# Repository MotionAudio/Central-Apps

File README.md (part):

<div align="center">

# Central

**A pedal for your pads and tracks, and apps for the rest of the worship team.**

[**Download the apps**](https://motionaudio.github.io/Central-Apps/) · [All releases](https://github.com/MotionAudio/Central-Apps/releases/latest) · [Install guide](INSTALL.md) · [What's new](release-notes/HISTORY.md)

</div>

---

I make Central for worship teams. The Central Pedal sits at the worship leader's feet and plays the pads, the multitracks and the click. Central Control runs the lights, slides, lyrics and in-ear mixes from the desk. Every musician gets their own chart and their own mix in Central Usage. This repository has all of it: the pedal's software, the six apps, the website and the tools that build them.

If you just want to install something, go to the [download page](https://motionaudio.github.io/Central-Apps/). It works out which file your computer or phone needs. Every file is also on the [latest release](https://github.com/MotionAudio/Central-Apps/releases/latest).

Sam

## The apps

| | App | Who uses it | What it's for |
|:-:|---|---|---|
|  | **Central Pedal** | The worship leader, on stage | A Raspberry Pi 4 that starts straight into the pedal. It plays ambient pads and multitracks with the click, spoken cues, charts and lyrics, and it can be the guitar or keys rig. You play it with 12 footswitches, knobs, a touch screen, an expression pedal, MIDI or a Stream Deck. |
|  | **Central Pedal Control** | Whoever gets the songs ready | The pedal's app on your computer, tablet or phone. Build the setlist at home, set up the pads and the controls, then press **⇪ Upload** and it all goes to the pedal. |
|  | **Central Control** | The main admin and admins | The desk. Lights, slides, lyrics, cameras, in-ear mixes, the tracks and the mix, for the whole service. |
|  | **Central Usage** | Musicians and singers | Your chord chart, the lyrics, your instrument and your own in-ear mix. |
|  | **Central Services** | Everyone in the church | The schedule. Who's playing which Sunday, and whether they said yes. |
|  | **Central Production** | Anyone who makes sounds | A studio for recording tracks and making loops, pads, instruments, plugins and pedal boards. Use what you make in your own apps or sell it through Make & sell. It's free, and it runs on a computer or in the browser with the same projects. |

## Versions and updates

All six apps share one version number. The second number is a full release (10.3, 10.4) and the third is a fix (10.4.1).

Central Pedal, Central Pedal Control and Central Production get updates for good. A Central Control or Central Usage key gets the next ten releases from when it was bought, so a key bought at 9.4 is covered through 10.4. Renewing costs $20 and covers ten more. Nobody has to renew; the apps keep working on the version they have. Central Services is a monthly plan and is always current.

Each app checks for a new version when it opens and once a day, and installs it by itself unless something is playing, in which case it asks first. Updates never touch songs, setlists, settings, keys or sign-ins. Every download is checked against the release's `SHA256SUMS` before anything is replaced.

## What runs where

| | Central Pedal | Central Pedal Control | Central Control | Central Usage | Central Services | Central Production |
|---|:-:|:-:|:-:|:-:|:-:|:-:|
| **Raspberry Pi 4** | ✅ | | | | | |
| **macOS** (Apple Silicon and Intel) | | ✅ | ✅ | ✅ | ✅ | ✅ |
| **Windows** 10 and 11 | | ✅ | ✅ | ✅ | ✅ | ✅ |
| **Linux** (.deb and AppImage) | | ✅ | ✅ | ✅ | ✅ | ✅ |
| **Android** | | ✅ | | ✅ | ✅ | |
| **iPhone and iPad** | | ¹ | | ¹ | ¹ | ² |

¹ The App Store versions are waiting on the Apple developer account ([IOS-APP-STORE.md](IOS-APP-STORE.md)). Until then, Central Usage runs in Safari from the main admin's computer, and Central Pedal Control runs in Safari from the pedal (`http://padpedal.local:8080/control/`, then Add to Home Screen).
² In the browser, on the website's Central Production page.

GitHub Actions builds and tests every release on every system before it's published.

## How it fits together

```mermaid
flowchart LR
  CT[("☁️ Central Tracks<br/>Motion Audio library")]
  PR["🎚️ Central Production<br/>computer · browser"]
  PC["🧰 Central Pedal Control<br/>Mac · Windows · Linux · Android"]
  CP["🎛️ Central Pedal<br/>Raspberry Pi 4"]
  CC["🖥️ Central Control<br/>main admin · admins"]
  CU["🎸 Central Usage<br/>musicians · singers"]
  OUT["Lights · slides · lyrics<br/>cameras · in-ear mixes"]
  PR -- "pads, sounds, tracks you make" --> PC
  CT -- "songs and tracks" --> PC
  CT -- "songs and tracks" --> CP
  PC -- "⇪ Upload" --> CP
  CP -- "every track, the click, pads, the instrument<br/>on their own channels over the network" --> CC
  CC --> OUT
  CC <-->|"chart, lyrics, your in-ear mix"| CU
```

## What it does

**Songs and tracks.** You can add a song from your own stems, from one WAV of the whole song (the stem splitter separates it on your computer into vocals, drums, bass, guitars, keys and the rest), from a MultiTracks.com or Loop Community download with its Ableton sections, or from Central Tracks. Planning Center plans come in with their songs, keys and arrangements. The pedal finds the tempo, key, beat grid and sections for you, and makes a click and a spoken guide from them. Key and tempo change on the fly without the stems drifting apart.

**On stage.** The Live screen shows the whole service. Safe Stop fades everything out over a couple of seconds if something goes wrong, the service lock stops anyone changing set-up mid-song, and a Ready check before the service catches a missing track or a click that would leak into the house. A second pedal can follow along silently as a backup and take over mid-song.

**The rig.** Guitar and bass pedalboards, with hundreds of free plugins on the Pi and a built-in rig on Windows and macOS. Keys from SoundFonts or your own plugins, with up to eight layers and splits. A tuner, an IR loader and a looper. On a computer you can use your own VST3, CLAP, Audio Unit and LV2 plugins, Kontakt and Keyscape included.

**The team.** Central Control pairs every device and gives each pedal its job. It runs DMX lights with 2,272 fixture profiles, slides and lyrics, NDI cameras, up to 64 in-ear mixes and talkback. Central Usage gives each musician their chart and mix, and practice mixes they can play at home.

**Making sounds.** Central Production records and mixes tracks with your own plugins, makes pads and instruments from samples, and has a plugin builder where you wire up your own effects. Everything you make can go straight into the other apps.

## Getting started

1. **Install the apps.** The [download page](https://motionaudio.github.io/Central-Apps/) picks the right file. [INSTALL.md](INSTALL.md) has the step-by-step for each system.
2. **Set up the pedal.** It arrives with its card in. Plug it in and set it up from your phone (below).
3. **Get your songs ready** in Central Pedal Control, then press **⇪ Upload** and type the pedal's name and code.
4. **Bring in the team.** The main admin installs Central Control, and the pedals and the musicians' devices pair with it.

### Setting up a Central Pedal

1. Plug in the power and your outputs. A screen on HDMI 1 is optional.
2. On your phone, join the Wi-Fi called **Central Pedal Setup**. The setup page opens by itself. If it doesn't, go to http://10.42.0.1.
3. Pick the church Wi-Fi and type its password.
4. Type a 4-digit code. If you use Central Control, use the main admin's code, which pairs the pedal with it. Otherwise any four digits will do. Central Pedal Control uses the same code.
5. Press **Upload**. The pedal joins the Wi-Fi and it's ready. If the password was wrong, Central Pedal Setup comes back after about a minute and the page tells you what happened.

When you move to a new building, **Settings → Network & devices → Turn the setup Wi-Fi on** runs it again.

### Building a card by hand

This is for people who build pedals. On an Ubuntu or Debian PC, from the folder you unzipped the newest `central-control-source.zip` into:

```bash
sudo WIFI_SSID="Church WiFi" WIFI_PASS="password" bash build-image.sh
```

The first build takes 40 to 60 minutes and needs the internet and about 15 GB free. You get `central-pedal-<version>.img`. Delete older images so nobody flashes one by mistake, and use a 16 GB card or bigger.

A few options you can set in front of the command:

- `PI_PASS=...` and `PI_HOSTNAME=...`
- `TFT=none` if there's no small screen, or another screen's id from `screens.json` (for example `TFT=waveshare35b`). The common blue 3.5" touch screen is on by default, and HDMI 1 still shows the full app.
- Leave out `WIFI_SSID` and the pedal makes its own **Central Pedal Setup** Wi-Fi for a phone.
- `FACTORY=0` skips the factory test.
- `I2S_DAC=off`, `SAFE_MODE=off`, `WIFI_COUNTRY=US`, `COMPRESS=1`
- `SOUNDS=small` leaves out the 1.2 GB grand piano, and `SOUNDS=none` leaves out the keys sound banks.

Flash it with Raspberry Pi Imager (*Choose OS → Use custom*, pick the `.img`, and answer **No** to *OS customisation*). The first start takes about a minute longer and restarts once. Wire the controls with `wiring.html`. Every part is optional, and the Learn tab can move any button or knob to any pin. A guitar needs a USB audio interface and a keyboard needs a USB MIDI port.

**The factory test.** A card from `build-image.sh` starts in a factory test. Plug a screen into HDMI 1 with a keyboard and mouse. It walks through every footswitch (its LED blinks), knob, slider, the expression pedal, the touch screen (a test pattern, its corners, calibration), the outputs, the instrument input, MIDI, Wi-Fi, temperature, power, storage and the sound banks. You can switch to a different touch screen there too. **Save report** keeps `factory-report.json` on the pedal. Press **Finish** and unplug it. The next start is the customer's: the test's Wi-Fi is forgotten, the touch screen setting stays, and it asks for the church Wi-Fi on their phone.

To add a Wi-Fi network later, put `pad-pedal-wifi.txt` on the card's `bootfs` partition (the network name on the first line, the password on the second), or use Settings on the pedal. To log in for maintenance: `ssh pi@padpedal.local`.

## Central Tracks

Central Tracks is the Motion Audio library, built into **Add a song → Central Tracks** on the pedal and in Central Pedal Control. You can search by song, artist or key. With Central Tracks Unlimited you can add anything; otherwise you buy the tracks you need, priced by each track's sound-quality grade. Teams publish their tracks on the Motion Audio website, and there are 20 hymns we arranged ourselves. Songs you import yourself never leave your devices. The server API is in [docs/CENTRAL-TRACKS-API.md](docs/CENTRAL-TRACKS-API.md).

## Documentation

| | |
|---|---|
| [INSTALL.md](INSTALL.md) | Installing and updating every app on every system |
| [IOS-APP-STORE.md](IOS-APP-STORE.md) | iPhone and iPad builds through TestFlight and the App Store |
| [DRIVE-SETUP.md](DRIVE-SETUP.md) | Keeping a copy of every release in Google Drive |
| [docs/SIGNING.md](docs/SIGNING.md) | Signing the Windows and Mac installers |
| [docs/DOMAIN-AND-EMAIL.md](docs/DOMAIN-AND-EMAIL.md) | Moving the website and email to motionaudio.org |
| [docs/PLANNING-CENTER-AND-CCLI.md](docs/PLANNING-CENTER-AND-CCLI.md) | Planning Center and CCLI |
| [docs/SHORTS.md](docs/SHORTS.md) | Automatic shorts and posting to social media |
| [docs/VIDEO.md](docs/VIDEO.md), [docs/VIDEO-INTEGRATION.md](docs/VIDEO-INTEGRATION.md) | Cameras, streaming and the video computer |
| [docs/PLUGIN-BUILDER.md](docs/PLUGIN-BUILDER.md) | Building plugins in Central Production |
| [docs/COMMUNITY-PLUGINS.md](docs/COMMUNITY-PLUGINS.md) | How community sounds, pedals and plugins are checked and paid for |
| [docs/CENTRAL-TRACKS-API.md](docs/CENTRAL-TRACKS-API.md) | The Central Tracks server API |
| [docs/DESIGN-SYSTEM.md](docs/DESIGN-SYSTEM.md), [docs/VOICE.md](docs/VOICE.md) | How the apps look, and how the words are written |
| [central-usage/README.md](central-usage/README.md) | Central Control and Central Usage in depth |
| [docs/brand/](docs/brand/) | The Motion Audio mark and the six app icons |
| [release-notes/](release-notes/) | The notes for every release |
| [The pedal's user guide](#the-pedals-user-guide) | Every tab of the Central Pedal, the hardware, the screens, MIDI and safe mode |

## What's new

**New in version 10.6.0:** Central Production can take a song all the way to the Central Pedal. Drag sections around and their music goes with them, move the whole song to a new key and tempo, add a click and spoken cues, check how loud it is and what Central Tracks will grade it, and export a pack the pedal reads with its sections marked. A MIDI footswitch or pad can run it too.

**New in version 10.4.2:** The website, the help guides, the manuals and the help inside the apps are rewritten in plain words, and the GitHub download page is up to date with all six apps.

**New in version 10.4.1:** On the pedal, Test sound now listens along the way and tells you where the sound stops, and fixes what it can. A pedal with only the headphone jack plays it directly. The pedal's screen is quicker.

**New in version 10.4.0:** In Central Production, a plugin knob is heard in about a fifth of a second, a MIDI keyboard plays through the track's plugins, exports keep plugin automation, and it uses noticeably less of the computer. Any delay in any app can follow the song's tempo.

**New in version 10.3.0:** Plugins play live on Central Production tracks without freezing. Shorts learn from what your church approves and post on a schedule. About twice as many pads, plugins, pedals, hymns, backgrounds and slide themes. A new website with pages for every app and sound pack, checkout, My products, Help and a status page.

**New in version 10.2.0:** Central Production arrived, along with the plugin builder, run sheets, the pre-service check, the band's screen, the slide designer, automatic shorts, Planning Center and CCLI, real light profiles and the Central Utility pack.

Older versions are in [release-notes/HISTORY.md](release-notes/HISTORY.md), and every release has its own notes in [release-notes/](release-notes/).

---

# The pedal's user guide

## The tabs

The tabs along the top are **Live, Pad, Tracks, Instrument, Looper, Controls, Learn** and **I/O**. Settings opens from the ⚙ button. On a keyboard, F8 is Live, F1 Pad, F2 Tracks, F3 Instrument, F9 Looper, F4 Controls, F5 Learn, F7 I/O and F6 Settings. You can also put *Show tab* on a footswitch.

### Live

This is the screen for the service. The setlist runs down the left, with a dot next to songs that have their tracks. Tap a song to load it; if something is playing, tap it twice.

The middle shows the song: its place in the setlist, key, BPM, time left and what's next. The sections are laid out in order, sized by length and coloured by type, and the one playing fills up as it goes. Tap a section to jump there on the next bar.

Under that are the transport buttons: previous section, play and pause, next section, **Vamp** (repeats this section until you press it again), **Safe Stop** and **Next song**. Safe Stop fades the tracks and pads out over 2.5 seconds; press it again to stop straight away. The pads, the instrument (with its tuner) and the meters are on the same screen.

Along the top you'll see the Pi's temperature, a low-power warning, the outputs, whether it's paired with the main admin, and two buttons:

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
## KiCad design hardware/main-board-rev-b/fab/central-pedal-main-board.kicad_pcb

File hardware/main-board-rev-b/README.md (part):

# Central Pedal main board - rev B

390 x 278 mm (rev B.3, the files in `fab/`; rev B.4 at 500 x 278 mm is being routed), 4 layers (signal / GND / 5V1 + 5V2 / signal), 1.6 mm, ENIG, black mask, white silk. The whole pedal on
one board: 10 footswitches with lights, 6 click-knobs (encoders), 2 faders, 18 label screens, the 7" Raspberry Pi
Touch Display 2 (ribbon), the 11.9" bar touch screen (HDMI 1 + USB), 6 mono 1/4" outputs, 2 instrument inputs,
2 external footswitch jacks, MIDI in / out, headphones, USB-C PD charging of a 2S battery, fan, power button. The
Raspberry Pi 4 sits under the board on the enclosure floor, component side toward it, on ~20 mm M2.5 standoffs - a
2x20 extra-long stacking header on its GPIO pins reaches the board's socket (the Pi's USB / Ethernet block is 16 mm
tall); a top plate sits 16 mm above the board.

The 7" Touch Display 2 and the 11.9" bar screen screw onto the front of the board (into their own stand-offs, screws
from the back); two slots in the board take the bar screen's HDMI and touch-USB plug bodies. The 40 mm fan and the Pi
mount in the enclosure base. You fit all of these yourself - the order and the parts are in `enclosure/README.md` and
`enclosure/central-pedal-blueprints.pdf`.

Rev B.3 (cost-down): HOOYA PJ-611E 1/4" jacks (3/8in bushing + nut through the back panel, $0.54 instead of $2.82),
generic EC11 encoders with a 30 mm shaft, onsemi ESD5Z5.0T1G ESD diodes, and SMT on the top side only (the bar-screen
ESD part moved to the front).

Wiring and pin map: `../../docs/MAIN-BOARD.md`. The layout that was approved: `layout-plan.png`.

## Ordering (PCBWay)

Everything PCBWay needs is in `fab/` - read `fab/PCBWAY-ORDER.md` first:

| File | What |
| --- | --- |
| `central-pedal-main-board-gerbers.zip` | Gerbers + Excellon drills + drill map (board edge included) |
| `central-pedal-main-board-bom-pcbway.csv` | BOM in PCBWay's layout: LCSC number + manufacturer part number for every part, sourcing notes; the last lines (type BOX BUILD) are the screens, fan, leads and hardware the assembler fits after soldering |
| `central-pedal-main-board-bom.csv` | the same BOM in JLC's layout |
| `central-pedal-main-board-cpl.csv` | Pick-and-place, both sides |
| `central-pedal-main-board-top.pdf` / `-bottom.pdf` | Assembly drawings (the silkscreen outlines show where the screens, the plugs and the fan go) |
| `board-with-screens.png`, `board-back-with-fan.png` | What the assembled board looks like, front and back |
| `*-front.png`, `*-back.png`, `*-in1.png`, `*-in2.png` | Renders of each copper layer |
| `central-pedal-main-board-netlist.txt` | Every net and the pins on it, for review |
| `design-notes.txt` | Every design assumption, numbered |
| `not-fitted.txt` | DNP parts |
| `drc-report.txt` | KiCad DRC of this exact board |
| `eeprom/` | HAT EEPROM settings (optional - the software finds the board by its chips too) |
| `*.kicad_pcb`, `*.kicad_pro`, `custom.pretty/` | The KiCad 7 project |

Parts LCSC does not stock - PCBWay sources them by description (the BOM's Notes column says what fits): the
10 PCB-pin soft-touch footswitches (M12, two pins 6.3-6.9 mm apart - the slotted holes take Taiwan Alpha SF12020F,
Tayda SF13P-0102-23.5R-M12, Love My Switches PCB-mount soft touch) and the 18 0.91" SSD1306 OLED modules (4-pin
I2C; both common pin orders fit with the 0R links) and the 6 EC11 encoders (30 mm D shaft, push switch, 20 detents /
20 pulses; the Bourns PEC11R-4230F-S0024 fits too). Everything else - including the jacks, the faders, the JST headers
and the Pi header - has an LCSC number and was in stock when this was made.

## Enclosure

A 3D-printed box for this board and the Pi: `enclosure/` (the blueprint PDF, STEP of the whole assembly, printable
tiles as STEP + STL, and the CadQuery script that generates them from the routed board). The Pi screws into threaded
inserts in the base floor and its Ethernet, two USB 3.0 and second HDMI come out on the right side panel through
panel-mount leads; the fan screws to the floor. The top plate sits 16 mm above the board with rounded
edges and chamfered windows; the footswitches come through it and take their nuts on top, the knobs come through plain
Ø 8 holes (the BOM's encoders have 30 mm shafts for this), the fader caps run in shallow recessed trays, and the two
touch screens (on the board, meeting the plate through foam gaskets) and 18 label screens sit behind bezelled windows. Read `enclosure/README.md` - it lists the dimensions
the model assumes that should be checked against the parts you actually buy, and the hardware (inserts, screws, knobs,
caps) to buy with it. `fab/PCBWAY-ORDER.md` has the PCBWay order settings step by step and how the parts are confirmed
with them.

## Regenerating

`design.py` is the whole design (every part, pin and net). On a machine with KiCad 7 (pcbnew Python + kicad-cli),
Java 17+ and Freerouting 1.9 (`/home/claude/tools/freerouting.jar` in the scripts), with an X display for
Freerouting (`Xvfb :99` is started by `route.py`):

```
python3 build.py                     # place parts, planes, outline, power trunks -> out/central-pedal-main-board.kicad_pcb
python3 fanout.py --pre              # plane-stub vias before routing (-> *-prefan.kicad_pcb + prefan.json)
python3 route.py 14 out/central-pedal-main-board-prefan.kicad_pcb   # Freerouting (pre-routes fixed), SES import, GND pours, DRC
python3 pass2.py                     # rip what crossed a hole / the slot, plane stubs in the wrong In2 band -> out/pass2-src.kicad_pcb
python3 route.py 10 out/pass2-src.kicad_pcb                          # route what is open again
python3 cleanup.py && python3 maze.py                                # tidy, then the grid router for the last connections
python3 pass3.py && python3 route.py 20 out/pass3-src.kicad_pcb --rippable   # optional: let Freerouting rip up and redo the signal routes
python3 fanout.py --stitch           # widen power tracks, GND stitching vias, final DRC
python3 screens.py && python3 cleanup.py out/pass6-src.kicad_pcb --no-helpers && python3 route.py 30 out/pass6-src.kicad_pcb
                                     # rev B.2: screen / fan mounting holes and the two plug slots on the routed board, then route what they cut
python3 cheapparts.py && python3 pass3.py && python3 route.py 25 out/pass3-src.kicad_pcb --rippable
python3 cleanup.py --no-helpers && python3 touchup.py && MAZE_VIA=80 python3 maze.py --margin 10
python3 fanout.py --stitch && python3 islandvias.py && python3 fixrefs.py && python3 upsizevias.py
                                     # rev B.3: PJ-611E jacks + D_BAR to the front, re-route, fan holes off, title rev B.3,
                                     # capacitor designators back in step with design.py, 0.3 mm drills where they fit
bash b4_pipeline.sh && bash finish_b4.sh
                                     # rev B.4: stretch.py widens the finished rev B.3 board to 500 mm along two seams
                                     # (footswitches 63.7 mm apart, faders / knobs evenly spaced), re-routes the strip,
                                     # the knob clusters and the wires over the seams, then finishes as above
python3 geometry.py                  # -> out/board-geometry.json for the enclosure
python3 export.py                    # -> out/fab/
```

Things learned on this board, built into the scripts: the pre-routes go to Freerouting as *fixed wires*, not as
keep-outs (oversized keep-outs walled in the pins next to them and most connections failed); holes without copper
and the ribbon slot get keep-outs (Freerouting cannot see them); the 5V1 plane polygon is cut where the 5V2 band
starts, because KiCad exports zone outlines, not fills; a wide trunk or a power via is never ripped by the helper
scripts (`trunkfix.py` puts any missing one back); `maze.py --rip REF PAD` clears the strip in front of a boxed-in
pin (`MAZE_VIA` sets what a via costs it, `MAZE_W` how greedy its search is; it straightens its own staircases).
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
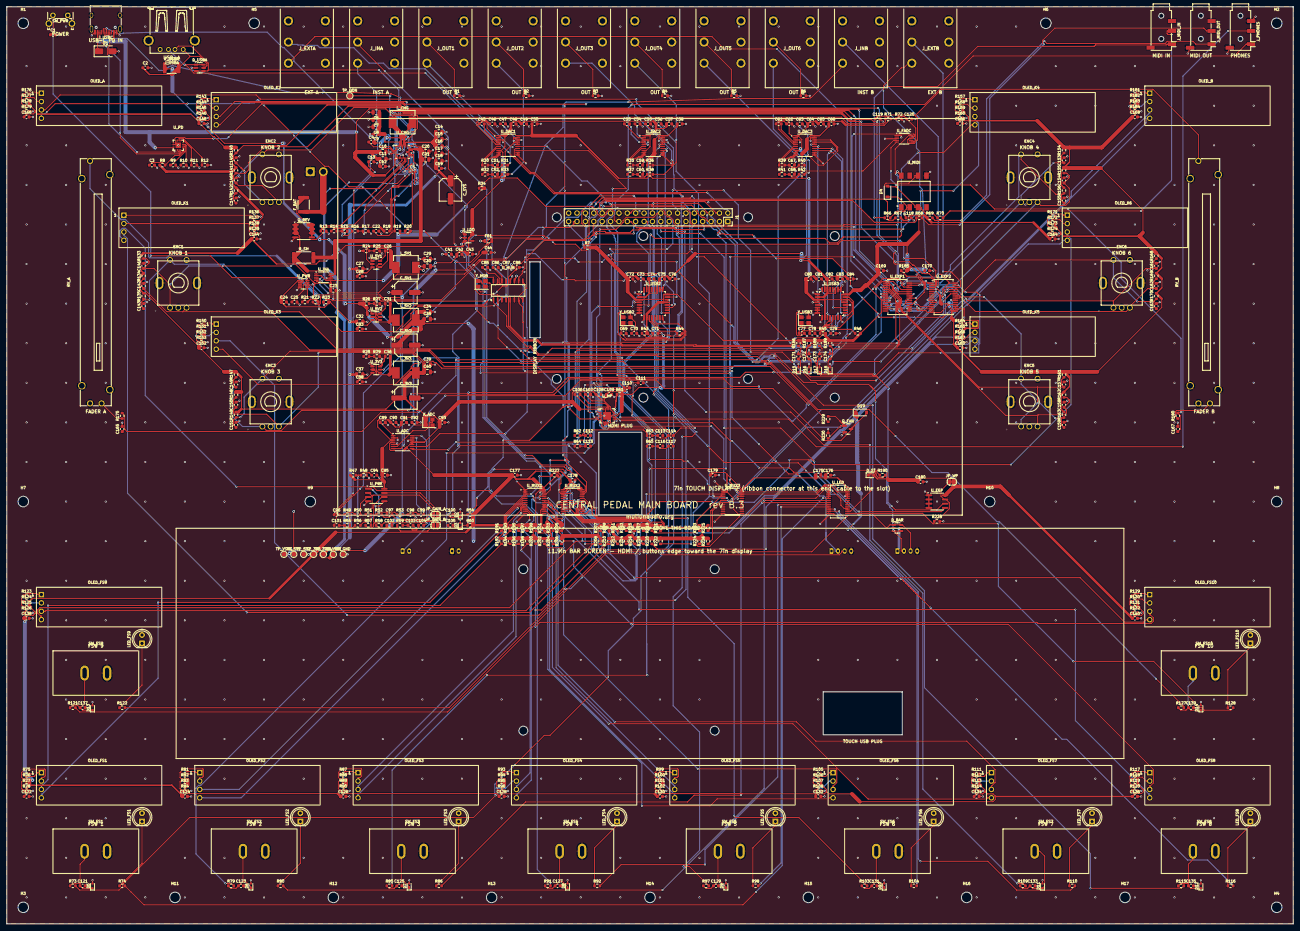
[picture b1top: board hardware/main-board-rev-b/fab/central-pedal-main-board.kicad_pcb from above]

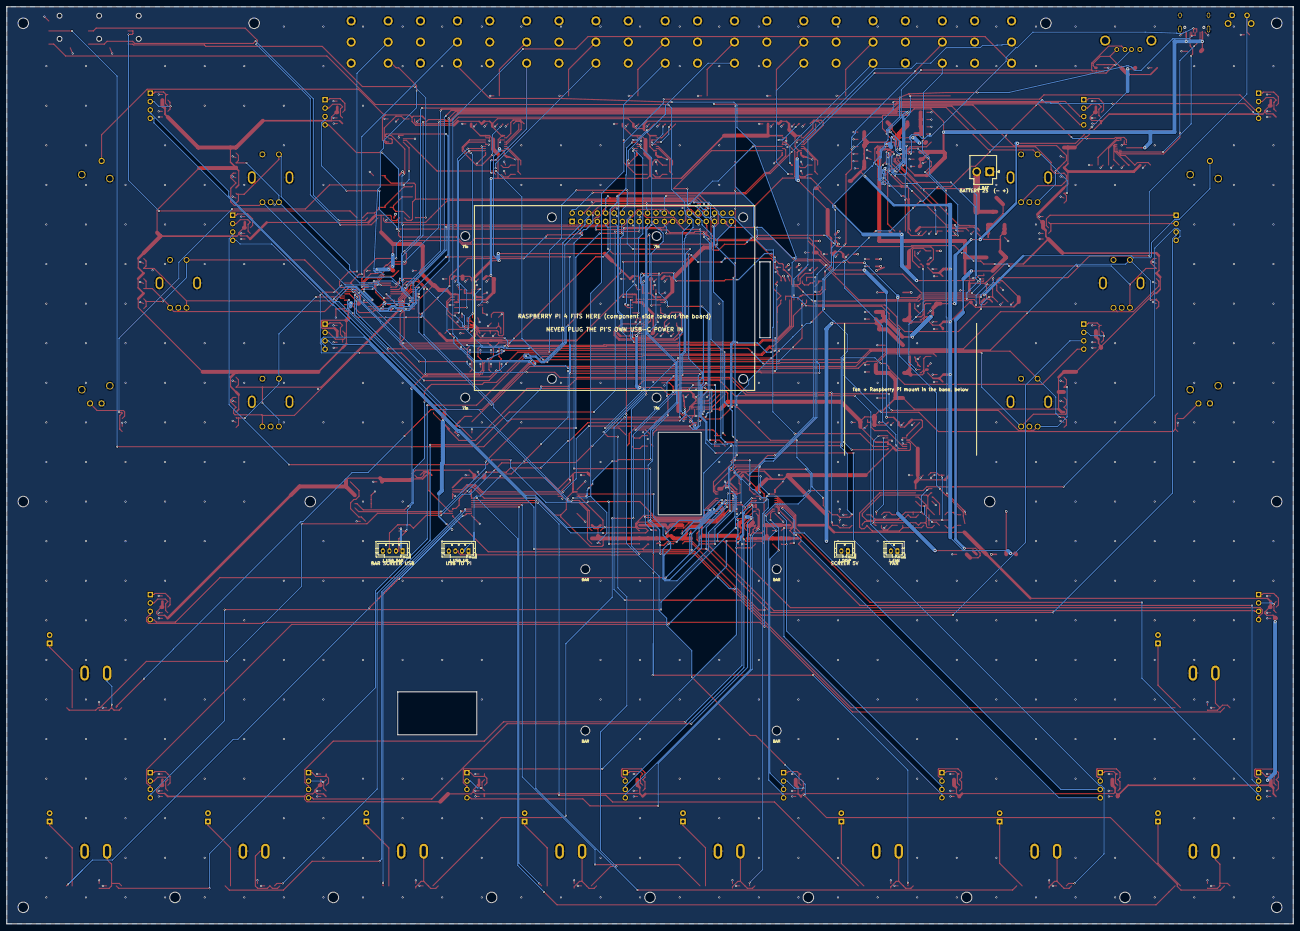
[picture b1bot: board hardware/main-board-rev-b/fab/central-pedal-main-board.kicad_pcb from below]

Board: 4 copper layers, 390.0 x 278.0 mm, 584 parts (5 on the bottom side), 319 nets.

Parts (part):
C1, C2, C9, C12, C19, C23, C26, C28, C31, C33, C36, C38, C48, C50, C56, C58, C64, C66, C72, C74, C76, C80, C82, C84, C88, C90, C92, C93, C95, C96, C100, C101, C105, C118, C119, C120, C121, C122, C123, C124, C125, C126, C127, C128, C129, C130, C131, C132, C133, C134, C135, C136, C137, C138, C139, C140, C144, C148, C152, C156, C160, C164, C165, C166, C167, C168, C169, C170, C171, C172, C173, C174, C175, C177, C178, C179, C180: 100n; C_0603_1608Metric
C3, C24, C25, C41, C42, C99, C104, C106, C107, C108, C109, C110, C111, C114, C117: 1u; C_0603_1608Metric
C4, C5: 47n; C_0603_1608Metric
C6, C7, C8, C10, C11, C14, C15, C16, C17, C18, C20, C21, C27, C32, C37: 10u; C_0805_2012Metric
C13, C85, C86: 4.7u; C_0603_1608Metric
C22, C98, C103: 1n; C_0603_1608Metric
C29, C30, C34, C35, C39, C40: 22u; C_0805_2012Metric
C43, C44, C49, C57, C65, C71, C73, C75, C79, C81, C83, C87, C89, C91, C94, C176: 10u; C_0603_1608Metric
C45, C46, C47, C53, C54, C55, C61, C62, C63: 2.2u; C_0603_1608Metric
C51, C52, C59, C60, C67, C68: 2.2n; C_0603_1608Metric
C69, C70, C77, C78: 22p; C_0603_1608Metric
C97, C102: 100p; C_0603_1608Metric
C112, C115: 33n; C_0603_1608Metric
C113, C116, C141, C142, C143, C145, C146, C147, C149, C150, C151, C153, C154, C155, C157, C158, C159, C161, C162, C163: 10n; C_0603_1608Metric
C_3V3, C_5V1, C_5V2: 100u 10V; CP_Elec_6.3x5.8
C_SYS: 100u 10V; CP_Elec_6.3x5.8
D1: SMAJ24A; D_SMA
D2, D3, D5, D6, D7, D8, D9, D10, D11, D12, D13, D14, D15, D16, D17, D18: ESD5Z5.0T1G; D_SOD-523
D4, D19: 1N4148W; D_SOD-123
D_BAR: USBLC6-2SC6; SOT-23-6
D_ST: GREEN; LED_0603_1608Metric
D_USBA: USBLC6-2SC6; SOT-23-6
ENC1: KNOB 1; Encoder_PEC11R_Vertical
ENC2: KNOB 2; Encoder_PEC11R_Vertical
ENC3: KNOB 3; Encoder_PEC11R_Vertical
ENC4: KNOB 4; Encoder_PEC11R_Vertical
ENC5: KNOB 5; Encoder_PEC11R_Vertical
ENC6: KNOB 6; Encoder_PEC11R_Vertical
FB1: FB 60R; L_0805_2012Metric
F_BAT: 7.5A PTC; Fuse_1812_4532Metric
F_USBA: 0.75A PTC; Fuse_1812_4532Metric
H1, H2, H3, H4, H5, H6, H7, H8, H9, H10, H11, H12, H13, H14, H15, H16, H17: M3; MountingHole_3.2mm_M3
HBAR_1, HBAR_2, HBAR_3, HBAR_4: bar screen stand-off M2.5; MountingHole_2.7mm
HD7_1, HD7_2, HD7_3, HD7_4: 7in display stand-off M2.5; MountingHole_2.7mm
HPI1, HPI2, HPI3, HPI4: MountingHole_2.7mm
J1: RASPBERRY PI 4; PinSocket_2x20_P2.54mm_Vertical
JP_GAIN_A: GAIN A 0dB; SolderJumper-2_P1.3mm_Open_RoundedPad1.0x1.5mm
JP_GAIN_B: GAIN B 0dB; SolderJumper-2_P1.3mm_Open_RoundedPad1.0x1.5mm
JP_WP: EEPROM WP; SolderJumper-2_P1.3mm_Open_RoundedPad1.0x1.5mm
J_BAT: JST VH 2; JST_VH_B2P-VH_1x02_P3.96mm_Vertical
J_DISP: JST PH 2; JST_PH_B2B-PH-K_1x02_P2.00mm_Vertical
J_EXTA: 1/4in TRS; Jack_6.35mm_HOOYA_PJ-611E_Horizontal
J_EXTB: 1/4in TRS; Jack_6.35mm_HOOYA_PJ-611E_Horizontal
J_FAN: JST PH 2; JST_PH_B2B-PH-K_1x02_P2.00mm_Vertical
J_INA: 1/4in TRS; Jack_6.35mm_HOOYA_PJ-611E_Horizontal
J_INB: 1/4in TRS; Jack_6.35mm_HOOYA_PJ-611E_Horizontal
J_MIDI_IN: 3.5mm TRRS; Jack_3.5mm_PJ320D_Horizontal
J_MIDI_OUT: 3.5mm TRRS; Jack_3.5mm_PJ320D_Horizontal
J_OUT1, J_OUT2, J_OUT3, J_OUT4, J_OUT5, J_OUT6: 1/4in TRS; Jack_6.35mm_HOOYA_PJ-611E_Horizontal
J_PHONES: 3.5mm TRRS; Jack_3.5mm_PJ320D_Horizontal
J_USBA: USB-A; USB_A_Horizontal_AF90
J_USBC: USB-C; USB_C_Receptacle_HRO_TYPE-C-31-M-12
J_USB_BAR: JST PH 4; JST_PH_B4B-PH-K_1x04_P2.00mm_Vertical
J_USB_UP: JST PH 4; JST_PH_B4B-PH-K_1x04_P2.00mm_Vertical
LED_FS1, LED_FS2, LED_FS3, LED_FS4, LED_FS5, LED_FS6, LED_FS7, LED_FS8, LED_FS9, LED_FS10: LED 5mm; LED_D5.0mm
L_3V3: 2.2uH; L_Sunlord_MWSA0603S
L_5V1, L_5V2: 3.3uH; L_Sunlord_MWSA0603S
L_CHG: 2.2uH; L_Sunlord_MWSA0603S
OLED_A: OLED 0.91in; OLED_091_I2C_Socket
OLED_B: OLED 0.91in; OLED_091_I2C_Socket
OLED_FS1, OLED_FS2, OLED_FS3, OLED_FS4, OLED_FS5, OLED_FS6, OLED_FS7, OLED_FS8, OLED_FS9, OLED_FS10: OLED 0.91in; OLED_091_I2C_Socket
OLED_K1, OLED_K2, OLED_K3, OLED_K4, OLED_K5, OLED_K6: OLED 0.91in; OLED_091_I2C_Socket
Q_FAN: AO3400A; SOT-23
Q_REV: AO4407A; SOIC-8_3.9x4.9mm_P1.27mm
R1, R2, R3, R4, R5, R6, R18, R31, R33, R36, R38, R40, R42, R50, R56, R73, R79, R85, R91, R97, R103, R109, R115, R121, R127, R229: 100R; R_0603_1608Metric
R7, R8, R70, R75, R76, R77, R78, R81, R82, R83, R84, R87, R88, R89, R90, R93, R94, R95, R96, R99, R100, R101, R102, R105, R106, R107, R108, R111, R112, R113, R114, R117, R118, R119, R120, R123, R124, R125, R126, R129, R130, R131, R132, R136, R137, R138, R139, R143, R144, R145, R146, R150, R151, R152, R153, R157, R158, R159, R160, R164, R165, R166, R167, R171, R172, R173, R174, R176, R177, R178, R179, R181, R182, R183, R184: 0R; R_0603_1608Metric
R9, R10: 900k; R_0603_1608Metric
R11: 11k; R_0603_1608Metric
R12, R15: 21k; R_0603_1608Metric
R13: 8.2k; R_0603_1608Metric
R14, R16, R19, R20, R25, R27, R29, R43, R45, R51, R54, R57, R60, R61, R133, R134, R135, R140, R141, R142, R147, R148, R149, R154, R155, R156, R161, R162, R163, R168, R169, R170, R185, R186, R187, R188, R189, R227, R228, R230: 10k; R_0603_1608Metric
R17, R72: 15k; R_0603_1608Metric
R21, R23, R34, R44, R46, R47, R48, R71: 100k; R_0603_1608Metric
R22, R53, R59, R191, R192, R193, R194, R195, R196, R197, R198, R199, R200, R201, R202, R203, R204, R205, R206, R207, R208, R209, R210, R211, R212, R213, R214, R215, R216, R217, R218, R219, R220, R221, R222, R223, R224, R225, R226: 4.7k; R_0603_1608Metric
R24, R26: 57.6k; R_0603_1608Metric
R28: 33.2k; R_0603_1608Metric
R30, R32, R35, R37, R39, R41: 470R; R_0603_1608Metric
R49, R55: 1M; R_0603_1608Metric
R52, R58: 30k; R_0603_1608Metric
R62, R64: 270R; R_0603_1608Metric
R63, R65: 150R; R_0603_1608Metric
R66: 220R; R_0603_1608Metric
R67: 2.2k; R_0603_1608Metric
R68: 10R; R_0603_1608Metric
R69: 33R; R_0603_1608Metric
R74, R80, R86, R92, R98, R104, R110, R116, R122, R128, R190: 330R; R_0603_1608Metric
R175, R180: 1k; R_0603_1608Metric
RV_A: 10k lin slide; Fader_PTA6043
RV_B: 10k lin slide; Fader_PTA6043
R_SH: 5mR; R_2512_6332Metric
SW_FS1: FOOTSWITCH 1; Footswitch_SPST_PCB
SW_FS2: FOOTSWITCH 2; Footswitch_SPST_PCB
SW_FS3: FOOTSWITCH 3; Footswitch_SPST_PCB
SW_FS4: FOOTSWITCH 4; Footswitch_SPST_PCB
SW_FS5: FOOTSWITCH 5; Footswitch_SPST_PCB
SW_FS6: FOOTSWITCH 6; Footswitch_SPST_PCB
SW_FS7: FOOTSWITCH 7; Footswitch_SPST_PCB
SW_FS8: FOOTSWITCH 8; Footswitch_SPST_PCB
SW_FS9: FOOTSWITCH 9; Footswitch_SPST_PCB
SW_FS10: FOOTSWITCH 10; Footswitch_SPST_PCB
SW_PWR: POWER; SW_Tactile_SPST_Angled_PTS645Vx39-2LFS
TP_3V3: 3V3; TestPoint_Pad_D1.5mm
TP_3V3A: 3V3A; TestPoint_Pad_D1.5mm
TP_5V1: 5V1; TestPoint_Pad_D1.5mm
TP_5V2: 5V2; TestPoint_Pad_D1.5mm
TP_GND: GND; TestPoint_Pad_D1.5mm
TP_QON: QON; TestPoint_Pad_D1.5mm
TP_VBAT: VBAT; TestPoint_Pad_D1.5mm
TP_VSYS: VSYS; TestPoint_Pad_D1.5mm
U_3V3, U_5V1, U_5V2: TPS565208DDCR; TSOT-23-6
U_ADC: PCM1808PWR; TSSOP-14_4.4x5mm_P0.65mm
U_CHG: BQ25798RQMR; BQ25798_VQFN-29_4x4
U_DAC1, U_DAC2, U_DAC3: PCM5102APWR; TSSOP-20_4.4x6.5mm_P0.65mm
U_EEP: CAT24C32WI-GT3; SOIC-8_3.9x4.9mm_P1.27mm
U_EXP1, U_EXP2: MCP23017-E/SS; SSOP-28_5.3x10.2mm_P0.65mm
U_FADC: ADS1115IDGSR; VSSOP-10_3x3mm_P0.5mm
U_HP: TPA6130A2RTJR; TPA6130A2_QFN-20_4x4
U_HUB: SL2.1A; SL2.1A_SOP-16
U_INA: INA226AIDGSR; VSSOP-10_3x3mm_P0.5mm
U_LDO: TLV75533PDBVR; SOT-23-5
U_LED: PCA9685PW; TSSOP-28_4.4x9.7mm_P0.65mm
U_MIDI: 6N138S; Opto_6N138S_SMD8
U_MUX1, U_MUX2, U_MUX3: TCA9548APWR; TSSOP-24_4.4x7.8mm_P0.65mm
U_PD: HUSB238A-BB001; HUSB238A_QFN-16_3x3
U_PRE: OPA1678IDR; SOIC-8_3.9x4.9mm_P1.27mm
U_PWR: LTC2954CTS8-1; TSOT-23-8
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
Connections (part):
3V3: C23.1, C39.1, C40.1, C50.1, C58.1, C66.1, C72.1, C73.1, C80.1, C81.1, C92.1, C93.1, C108.1, C109.1, C122.1, C124.1, C126.1, C128.1, C130.1, C132.1, C134.1, C136.1, C138.1, C140.1, C144.1, C148.1, C152.1, C156.1, C160.1, C164.1, C166.1, C168.1, C169.1, C170.1, C175.1, C176.1, C177.1, C178.1, C179.1, C180.1, C_3V3.1, D_ST.2, JP_WP.2, L_3V3.2, R7.2, R8.1, R19.2, R20.2, R21.2, R22.2, R28.1, R34.2, R43.2, R44.2, R45.2, R46.2, R54.2, R60.2, R61.2, R67.2, R69.1, R76.2, R77.2, R82.2, R83.2, R88.2, R89.2, R94.2, R95.2, R100.2, R101.2, R106.2, R107.2, R112.2, R113.2, R118.2, R119.2, R124.2, R125.2, R130.2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
3V3A: C42.1, C43.1, C48.1, C49.1, C56.1, C57.1, C64.1, C65.1, C74.1, C75.1, C76.1, C82.1, C83.1, C84.1, C119.1, RV_A.3, RV_B.3, TP_3V3A.1, U_DAC1.1, U_DAC1.8, U_DAC2.1, U_DAC2.8, U_DAC3.1, U_DAC3.8, U_FADC.8, U_LDO.5, U_USB2.2, U_USB2.27, U_USB2.30, U_USB3.2, U_USB3.27, U_USB3.30
5V1: C29.1, C30.1, C41.1, C87.1, C88.1, C118.1, C_5V1.1, FB1.1, J1.2, J1.4, L_5V1.2, R24.1, TP_5V1.1, U_HUB.11, U_LDO.1, U_LDO.3, U_MIDI.8
5V2: C34.1, C35.1, C_5V2.1, D19.1, D_BAR.5, F_USBA.1, J_DISP.2, J_FAN.2, J_USB_BAR.1, LED_FS1.2, LED_FS2.2, LED_FS3.2, LED_FS4.2, LED_FS5.2, LED_FS6.2, LED_FS7.2, LED_FS8.2, LED_FS9.2, LED_FS10.2, L_5V2.2, R26.1, TP_5V2.1
5VA: C44.1, C90.1, C91.1, C95.1, FB1.2, R47.1, U_ADC.3, U_PRE.8
ADC_INL: C99.2, U_ADC.13
ADC_INR: C104.2, U_ADC.14
ADC_RC_A: C98.1, C99.1, R53.2
ADC_RC_B: C103.1, C104.1, R59.2
ADC_SCK: U_ADC.6, X_ADC.3
ADC_VREF: C89.1, U_ADC.1
BAR_DM: D_BAR.3, D_BAR.4, J_USB_BAR.2, U_HUB.1
BAR_DP: D_BAR.1, D_BAR.6, J_USB_BAR.3, U_HUB.2
BAT_F: F_BAT.2, Q_REV.5, Q_REV.6, Q_REV.7, Q_REV.8
BAT_RAW: F_BAT.1, J_BAT.2
BCK2: U_DAC2.13, U_USB2.19
BCK3: U_DAC3.13, U_USB3.19
BST1: C4.1, U_CHG.4
BST2: C5.1, U_CHG.19
BST_3V3: C36.1, U_3V3.6
BST_5V1: C26.1, U_5V1.6
BST_5V2: C31.1, U_5V2.6
CAPM1: C45.2, U_DAC1.4
CAPM2: C53.2, U_DAC2.4
CAPM3: C61.2, U_DAC3.4
CAPP1: C45.1, U_DAC1.2
CAPP2: C53.1, U_DAC2.2
CAPP3: C61.1, U_DAC3.2
CC1: J_USBC.A5, U_PD.3
CC2: J_USBC.B5, U_PD.4
CHG_BATP: R18.2, U_CHG.18
CHG_ILIM: R14.2, R15.1, U_CHG.17
CHG_INT: R20.1, U_CHG.21, U_EXP2.3
CHG_PROG: R13.1, U_CHG.20
CHG_QON: TP_QON.1, U_CHG.12
CHG_SDRV: C22.1, U_CHG.24
CHG_STAT: R19.1, U_CHG.1, U_EXP2.1
CHG_TS: R16.2, R17.1, U_CHG.16
CPN: C106.2, U_HP.17
CPP: C106.1, U_HP.18
CPVSS: C107.1, U_HP.15, U_HP.16
DAC1_L: R30.1, U_DAC1.6
DAC1_R: R32.1, U_DAC1.7
DAC2_L: R35.1, U_DAC2.6
DAC2_R: R37.1, U_DAC2.7
DAC3_L: R39.1, U_DAC3.6
DAC3_R: R41.1, U_DAC3.7
DAC_XSMT: J1.13, R34.1, U_DAC1.17
DIN2: U_DAC2.14, U_USB2.17
DIN3: U_DAC3.14, U_USB3.17
EEP_WP: JP_WP.1, R228.1, U_EEP.7
ENC1A: C141.1, ENC1.1, R133.1, U_EXP1.21
ENC1B: C142.1, ENC1.3, R134.1, U_EXP1.22
ENC1S: C143.1, ENC1.4, R135.1, U_EXP1.5
ENC2A: C145.1, ENC2.1, R140.1, U_EXP1.23
ENC2B: C146.1, ENC2.3, R141.1, U_EXP1.24
ENC2S: C147.1, ENC2.4, R142.1, U_EXP1.6
ENC3A: C149.1, ENC3.1, R147.1, U_EXP1.25
ENC3B: C150.1, ENC3.3, R148.1, U_EXP1.26
ENC3S: C151.1, ENC3.4, R149.1, U_EXP1.7
ENC4A: C153.1, ENC4.1, R154.1, U_EXP1.27
ENC4B: C154.1, ENC4.3, R155.1, U_EXP1.28
ENC4S: C155.1, ENC4.4, R156.1, U_EXP1.8
ENC5A: C157.1, ENC5.1, R161.1, U_EXP1.1
ENC5B: C158.1, ENC5.3, R162.1, U_EXP1.2
ENC5S: C159.1, ENC5.4, R163.1, U_EXP2.21
ENC6A: C161.1, ENC6.1, R168.1, U_EXP1.3
ENC6B: C162.1, ENC6.3, R169.1, U_EXP1.4
ENC6S: C163.1, ENC6.4, R170.1, U_EXP2.22
EN_PWR: R23.1, U_3V3.5, U_5V1.5, U_5V2.5, U_PWR.6
EXP1_INT: J1.16, U_EXP1.20
EXP2_INT: J1.22, U_EXP2.20
EXP_RST: R185.1, U_EXP1.18, U_EXP2.18
EXTA_R: C172.1, D16.1, J_EXTA.R, R187.1, U_EXP2.24
EXTA_T: C171.1, D15.1, J_EXTA.T, R186.1, U_EXP2.23
EXTB_R: C174.1, D18.1, J_EXTB.R, R189.1, U_EXP2.26
EXTB_T: C173.1, D17.1, J_EXTB.T, R188.1, U_EXP2.25
F1_L: C51.1, R30.2, R31.1
F1_R: C52.1, R32.2, R33.1
F2_L: C59.1, R35.2, R36.1
F2_R: C60.1, R37.2, R38.1
F3_L: C67.1, R39.2, R40.1
F3_R: C68.1, R41.2, R42.1
FAD_A_ADC: C165.1, R175.2, U_FADC.4
FAD_A_W: R175.1, RV_A.2
FAD_B_ADC: C167.1, R180.2, U_FADC.5
FAD_B_W: R180.1, RV_B.2
FAN_CTL: J1.37, R229.1
FAN_G: Q_FAN.1, R229.2, R230.1
FAN_N: D19.2, J_FAN.1, Q_FAN.3
FB_3V3: R28.2, R29.1, U_3V3.4
FB_5V1: R24.2, R25.1, U_5V1.4
FB_5V2: R26.2, R27.1, U_5V2.4
FS1: C121.1, D5.1, R73.1, SW_FS1.1
FS2: C123.1, D6.1, R79.1, SW_FS2.1
FS3: C125.1, D7.1, R85.1, SW_FS3.1
FS4: C127.1, D8.1, R91.1, SW_FS4.1
FS5: C129.1, D9.1, R97.1, SW_FS5.1
FS6: C131.1, D10.1, R103.1, SW_FS6.1
FS7: C133.1, D11.1, R109.1, SW_FS7.1
FS8: C135.1, D12.1, R115.1, SW_FS8.1
FS9: C137.1, D13.1, R121.1, SW_FS9.1
FS10: C139.1, D14.1, R127.1, SW_FS10.1
GND: C1.2, C2.2, C3.2, C6.2, C7.2, C8.2, C9.2, C10.2, C11.2, C12.2, C13.2, C14.2, C15.2, C16.2, C17.2, C18.2, C19.2, C20.2, C21.2, C22.2, C23.2, C24.2, C25.2, C27.2, C28.2, C29.2, C30.2, C32.2, C33.2, C34.2, C35.2, C37.2, C38.2, C39.2, C40.2, C41.2, C42.2, C43.2, C44.2, C46.2, C47.2, C48.2, C49.2, C50.2, C51.2, C52.2, C54.2, C55.2, C56.2, C57.2, C58.2, C59.2, C60.2, C62.2, C63.2, C64.2, C65.2, C66.2, C67.2, C68.2, C69.2, C70.2, C71.2, C72.2, C73.2, C74.2, C75.2, C76.2, C77.2, C78.2, C79.2, C80.2, C81.2, C82.2, C83.2, C84.2, C85.2, C86.2, C87.2, C88.2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
GND_R1: J_OUT1.R, R1.1
GND_R2: J_OUT2.R, R2.1
GND_R3: J_OUT3.R, R3.1
GND_R4: J_OUT4.R, R4.1
GND_R5: J_OUT5.R, R5.1
GND_R6: J_OUT6.R, R6.1
GPIO_FS1: J1.29, R73.2
GPIO_FS2: J1.31, R79.2
GPIO_FS3: J1.26, R85.2
GPIO_FS4: J1.24, R91.2
GPIO_FS5: J1.21, R97.2
GPIO_FS6: J1.19, R103.2
GPIO_FS7: J1.23, R109.2
GPIO_FS8: J1.36, R115.2
GPIO_FS9: J1.11, R121.2
GPIO_FS10: J1.15, R127.2
HP_GL: C110.1, U_HP.2
HP_GR: C111.1, U_HP.4
HP_INL: C114.2, U_HP.1
HP_INR: C117.2, U_HP.5
HP_L: J_PHONES.T, U_HP.14
HP_R: J_PHONES.R1, U_HP.11
HP_SD: R61.1, U_HP.6, U_LED.18
HUB_18: C86.1, U_HUB.14
HUB_33: C85.1, U_HUB.13
HUB_DM1: U_HUB.7, U_USB2.22
HUB_DM2: U_HUB.5, U_USB3.22
HUB_DP1: U_HUB.8, U_USB2.23
HUB_DP2: U_HUB.6, U_USB3.23
HUB_XI: U_HUB.16, Y_HUB.1
HUB_XO: U_HUB.15, Y_HUB.3
I2S_BCK: J1.12, U_ADC.8, U_DAC1.13
I2S_DIN: J1.38, U_ADC.9
I2S_DOUT: J1.40, U_DAC1.14
I2S_LRCK: J1.35, U_ADC.7, U_DAC1.15
ID_SC: J1.28, U_EEP.6
ID_SD: J1.27, U_EEP.5
INST_A: C96.1, J_INA.T
INST_B: C101.1, J_INB.T
INST_DET_A: C100.1, D2.1, J_INA.R, R54.1, U_EXP2.27
INST_DET_B: C105.1, D3.1, J_INB.R, R60.1, U_EXP2.28
IN_AC_A: C96.2, R49.1, R50.1
IN_AC_B: C101.2, R55.1, R56.1
LDOO1: C47.1, U_DAC1.18
LDOO2: C55.1, U_DAC2.18
LDOO3: C63.1, U_DAC3.18
LED1: R74.2, U_LED.6
LED2: R80.2, U_LED.7
LED3: R86.2, U_LED.8
LED4: R92.2, U_LED.9
LED5: R98.2, U_LED.10
LED6: R104.2, U_LED.11
LED7: R110.2, U_LED.12
LED8: R116.2, U_LED.13
LED9: R122.2, U_LED.15
LED10: R128.2, U_LED.16
LEDK1: LED_FS1.1, R74.1
LEDK2: LED_FS2.1, R80.1
LEDK3: LED_FS3.1, R86.1
LEDK4: LED_FS4.1, R92.1
LEDK5: LED_FS5.1, R98.1
LEDK6: LED_FS6.1, R104.1
LEDK7: LED_FS7.1, R110.1
LEDK8: LED_FS8.1, R116.1
LEDK9: LED_FS9.1, R122.1
LEDK10: LED_FS10.1, R128.1
LED_ST: R190.2, U_LED.17
LED_ST_K: D_ST.1, R190.1
LRCK2: U_DAC2.15, U_USB2.5
LRCK3: U_DAC3.15, U_USB3.5
MIDI_A: D4.1, R66.2, U_MIDI.2
MIDI_IN_R: J_MIDI_IN.R1, R70.2
MIDI_IN_T: J_MIDI_IN.T, R66.1
MIDI_K: D4.2, R70.1, U_MIDI.3
MIDI_OUT_R: J_MIDI_OUT.R1, R68.2
MIDI_OUT_T: J_MIDI_OUT.T, R69.2
MIDI_RX: J1.10, R67.1, U_MIDI.6
MIDI_TX: J1.8, R68.1
MUX_RST: R227.1, U_MUX1.3, U_MUX2.3, U_MUX3.3
OLED_A_P1: OLED_A.1, R176.1, R178.1
OLED_A_P2: OLED_A.2, R177.1, R179.1
OLED_B_P1: OLED_B.1, R181.1, R183.1
OLED_B_P2: OLED_B.2, R182.1, R184.1
OLED_FS1_P1: OLED_FS1.1, R75.1, R77.1
OLED_FS1_P2: OLED_FS1.2, R76.1, R78.1
OLED_FS2_P1: OLED_FS2.1, R81.1, R83.1
OLED_FS2_P2: OLED_FS2.2, R82.1, R84.1
OLED_FS3_P1: OLED_FS3.1, R87.1, R89.1
OLED_FS3_P2: OLED_FS3.2, R88.1, R90.1
OLED_FS4_P1: OLED_FS4.1, R93.1, R95.1
OLED_FS4_P2: OLED_FS4.2, R94.1, R96.1
OLED_FS5_P1: OLED_FS5.1, R99.1, R101.1
OLED_FS5_P2: OLED_FS5.2, R100.1, R102.1
OLED_FS6_P1: OLED_FS6.1, R105.1, R107.1
OLED_FS6_P2: OLED_FS6.2, R106.1, R108.1
OLED_FS7_P1: OLED_FS7.1, R111.1, R113.1
OLED_FS7_P2: OLED_FS7.2, R112.1, R114.1
OLED_FS8_P1: OLED_FS8.1, R117.1, R119.1
OLED_FS8_P2: OLED_FS8.2, R118.1, R120.1
OLED_FS9_P1: OLED_FS9.1, R123.1, R125.1
OLED_FS9_P2: OLED_FS9.2, R124.1, R126.1
OLED_FS10_P1: OLED_FS10.1, R129.1, R131.1
OLED_FS10_P2: OLED_FS10.2, R130.1, R132.1
OLED_K1_P1: OLED_K1.1, R136.1, R138.1
OLED_K1_P2: OLED_K1.2, R137.1, R139.1
OLED_K2_P1: OLED_K2.1, R143.1, R145.1
OLED_K2_P2: OLED_K2.2, R144.1, R146.1
OLED_K3_P1: OLED_K3.1, R150.1, R152.1
OLED_K3_P2: OLED_K3.2, R151.1, R153.1
OLED_K4_P1: OLED_K4.1, R157.1, R159.1
OLED_K4_P2: OLED_K4.2, R158.1, R160.1
OLED_K5_P1: OLED_K5.1, R164.1, R166.1
OLED_K5_P2: OLED_K5.2, R165.1, R167.1
OLED_K6_P1: OLED_K6.1, R171.1, R173.1
OLED_K6_P2: OLED_K6.2, R172.1, R174.1
OUT1: J_OUT1.T, R31.2
OUT2: J_OUT2.T, R33.2
OUT3: J_OUT3.T, R36.2
OUT4: J_OUT4.T, R38.2
OUT5: J_OUT5.T, R40.2
OUT6: J_OUT6.T, R42.2
PB: C1.1, SW_PWR.1, U_PWR.2
PDT: C25.1, U_PWR.7
PD_DBG: R9.1, U_PD.6
PD_FAULT: U_EXP2.2, U_PD.13
PD_HVDCP: R10.1, U_PD.7
PD_ISET: R12.1, U_PD.10
PD_VDD: C3.1, R8.2, U_PD.5
PD_VSET: R11.1, U_PD.9
PI_3V3: J1.1, J1.17, R7.1
PMID: C6.1, C7.1, C8.1, C9.1, U_CHG.29
PRE_A: C97.1, JP_GAIN_A.1, R52.1, R53.1, U_PRE.1
PRE_AN: C97.2, JP_GAIN_A.2, R51.1, R52.2, U_PRE.2
PRE_AP: R50.2, U_PRE.3
PRE_B: C102.1, JP_GAIN_B.1, R58.1, R59.1, U_PRE.7
PRE_BN: C102.2, JP_GAIN_B.2, R57.1, R58.2, U_PRE.6
PRE_BP: R56.2, U_PRE.5
PWF1_L: C112.1, R62.2, R63.1
PWF1_R: C115.1, R64.2, R65.1
PWF2_L: C113.1, C114.1, R63.2
PWF2_R: C116.1, C117.1, R65.2
PWM_L: J1.32, R62.1
PWM_R: J1.33, R64.1
PWR_INT: J1.7, R21.1, U_PWR.5
PWR_KILL: J1.18, R22.1, U_PWR.8
REGN: C13.1, R14.1, R16.1, U_CHG.5
ROMDT2: R43.1, U_USB2.15
ROMDT3: R45.1, U_USB3.15
SCL: J1.5, U_CHG.14, U_EXP1.12, U_EXP2.12, U_FADC.10, U_HP.8, U_INA.5, U_LED.26, U_MUX1.22, U_MUX2.22, U_MUX3.22
SC_OLED_A: OLED_A.3, R224.1, U_MUX3.5
SC_OLED_B: OLED_B.3, R226.1, U_MUX3.7
SC_OLED_FS1: OLED_FS1.3, R192.1, U_MUX1.5
SC_OLED_FS2: OLED_FS2.3, R194.1, U_MUX1.7
SC_OLED_FS3: OLED_FS3.3, R196.1, U_MUX1.9
SC_OLED_FS4: OLED_FS4.3, R198.1, U_MUX1.11
SC_OLED_FS5: OLED_FS5.3, R200.1, U_MUX1.14
SC_OLED_FS6: OLED_FS6.3, R202.1, U_MUX1.16
SC_OLED_FS7: OLED_FS7.3, R204.1, U_MUX1.18
SC_OLED_FS8: OLED_FS8.3, R206.1, U_MUX1.20
SC_OLED_FS9: OLED_FS9.3, R208.1, U_MUX2.5
SC_OLED_FS10: OLED_FS10.3, R210.1, U_MUX2.7
SC_OLED_K1: OLED_K1.3, R212.1, U_MUX2.9
SC_OLED_K2: OLED_K2.3, R214.1, U_MUX2.11
SC_OLED_K3: OLED_K3.3, R216.1, U_MUX2.14
SC_OLED_K4: OLED_K4.3, R218.1, U_MUX2.16
SC_OLED_K5: OLED_K5.3, R220.1, U_MUX2.18
SC_OLED_K6: OLED_K6.3, R222.1, U_MUX2.20
SDA: J1.3, U_CHG.15, U_EXP1.13, U_EXP2.13, U_FADC.9, U_HP.7, U_INA.4, U_LED.27, U_MUX1.23, U_MUX2.23, U_MUX3.23
SD_OLED_A: OLED_A.4, R223.1, U_MUX3.4
SD_OLED_B: OLED_B.4, R225.1, U_MUX3.6
SD_OLED_FS1: OLED_FS1.4, R191.1, U_MUX1.4
SD_OLED_FS2: OLED_FS2.4, R193.1, U_MUX1.6
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
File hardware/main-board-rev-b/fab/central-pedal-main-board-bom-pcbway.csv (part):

Item #,Designator,Qty,Manufacturer,Mfg Part #,Description / Value,Package/Footprint,Type,Your Instructions / Notes
1,"C1,C2,C9,C12,C19,C23,C26,C28,C31,C33,C36,C38,C48,C50,C56,C58,C64,C66,C72,C74,C76,C80,C82,C84,C88,C90,C92,C93,C95,C96,C100,C101,C105,C118,C119,C120,C121,C122,C123,C124,C125,C126,C127,C128,C129,C130,C131,C132,C133,C134,C135,C136,C137,C138,C139,C140,C144,C148,C152,C156,C160,C164,C165,C166,C167,C168,C169,C170,C171,C172,C173,C174,C175,C177,C178,C179,C180",77,,,100n,C_0603_1608Metric,SMD,LCSC C14663.
2,"C3,C24,C25,C41,C42,C99,C104,C106,C107,C108,C109,C110,C111,C114,C117",15,,,1u,C_0603_1608Metric,SMD,LCSC C5673.
3,"C4,C5",2,,,47n,C_0603_1608Metric,SMD,LCSC C1622.
4,"C6,C7,C8,C10,C11,C14,C15,C16,C17,C18,C20,C21,C27,C32,C37",15,,,10u,C_0805_2012Metric,SMD,LCSC C15850.
5,"C13,C85,C86",3,,,4.7u,C_0603_1608Metric,SMD,LCSC C69335.
6,"C22,C98,C103",3,,,1n,C_0603_1608Metric,SMD,LCSC C1588.
7,"C29,C30,C34,C35,C39,C40",6,,,22u,C_0805_2012Metric,SMD,LCSC C29277.
8,"C43,C44,C49,C57,C65,C71,C73,C75,C79,C81,C83,C87,C89,C91,C94,C176",16,,,10u,C_0603_1608Metric,SMD,LCSC C19702.
9,"C45,C46,C47,C53,C54,C55,C61,C62,C63",9,,,2.2u,C_0603_1608Metric,SMD,LCSC C23630.
10,"C51,C52,C59,C60,C67,C68",6,,,2.2n,C_0603_1608Metric,SMD,LCSC C1604.
11,"C69,C70,C77,C78",4,,,22p,C_0603_1608Metric,SMD,LCSC C1653.
12,"C97,C102",2,,,100p,C_0603_1608Metric,SMD,LCSC C14858.
13,"C112,C115",2,,,33n,C_0603_1608Metric,SMD,LCSC C21117.
14,"C113,C116,C141,C142,C143,C145,C146,C147,C149,C150,C151,C153,C154,C155,C157,C158,C159,C161,C162,C163",20,,,10n,C_0603_1608Metric,SMD,LCSC C57112.
15,"C_3V3,C_5V1,C_5V2,C_SYS",4,,100uF 10V polymer 6.3x6,100u 10V,CP_Elec_6.3x5.8,SMD,LCSC C48971041.
16,D1,1,,SMAJ24A TVS,VBUS surge clamp - SMAJ24A,D_SMA,SMD,LCSC C113962.
17,"D2,D3,D5,D6,D7,D8,D9,D10,D11,D12,D13,D14,D15,D16,D17,D18",16,onsemi,ESD5Z5.0T1G,ESD5Z5.0T1G,D_SOD-523,SMD,LCSC C82044.
18,"D4,D19",2,,1N4148W,1N4148W,D_SOD-123,SMD,LCSC C81598.
19,D_ST,1,,0603 green LED (KENTO KT-0603G),Status LED (driver running) - GREEN,LED_0603_1608Metric,SMD,LCSC C12624.
20,"D_BAR,D_USBA",2,ST,USBLC6-2SC6,USBLC6-2SC6,SOT-23-6,SMD,LCSC C7519.
21,"ENC1,ENC2,ENC3,ENC4,ENC5,ENC6",6,,"EC11 encoder, push switch, 30 mm 6 mm D shaft, 20 detents / 20 pulses (generic; Bourns PEC11R-4230F-S0024 fits too)",Knob,Encoder_PEC11R_Vertical,TH,"Generic EC11 incremental encoder WITH push switch: 30 mm shaft length (from the mounting face), 6 mm D / half-moon metal shaft, detents = pulses (20 detents / 20 pulses; 24/24 also fine - NOT 30/15). Taobao: 'EC11 编码器 带开关 20脉冲 半轴 30mm'. If none: Bourns PEC11R-4230F-S0024 (LCSC C7435302). No nut."
22,FB1,1,Murata,BLM21PG600SN1D,Ferrite bead 60R@100MHz 3.5 A - FB 60R,L_0805_2012Metric,SMD,LCSC C18305.
23,F_BAT,1,,SMD1812-750-12V (7.5 A hold PTC),Battery fuse - 7.5A PTC,Fuse_1812_4532Metric,SMD,LCSC C3039825.
24,F_USBA,1,Bourns,MF-MSMF075-2 (0.75 A hold PTC 1812),USB-A port fuse - 0.75A PTC,Fuse_1812_4532Metric,SMD,LCSC C84140.
25,J1,1,,"2x20 female header 2.54 mm, 8.5 mm tall (Pi on ~20 mm M2.5 standoffs with a 2x20 extra-long stacking header on its GPIO pins)",Raspberry Pi 4 GPIO (Pi behind the board) - RASPBERRY PI 4,PinSocket_2x20_P2.54mm_Vertical,TH,"LCSC C5124634. 2x20 female header, 8.5 mm tall, on the BACK of the board (the Pi plugs on from behind through a stacking header; pin 1 = left end, inner row, seen from the front)."
26,J_BAT,1,JST,B2P-VH(LF)(SN),"2S battery pack (with its own BMS), 10 A connector - JST VH 2",JST_VH_B2P-VH_1x02_P3.96mm_Vertical,TH,"LCSC C160315. JST VH 2-pin, back side (battery)."
27,"J_DISP,J_FAN",2,JST,B2B-PH-K-S,JST PH 2,JST_PH_B2B-PH-K_1x02_P2.00mm_Vertical,TH,"LCSC C5251182. JST PH 2-pin, back side (fan, 7-inch display power)."
28,"J_EXTA,J_EXTB,J_INA,J_INB,J_OUT1,J_OUT2,J_OUT3,J_OUT4,J_OUT5,J_OUT6",10,,HOOYA PJ-611E,1/4in TRS,Jack_6.35mm_HOOYA_PJ-611E_Horizontal,TH,"LCSC C309282. HOOYA PJ-611E 6.35 mm stereo switched jack, horizontal, 3/8in threaded bushing. Body flat on the board, front face on the board edge. Supplied nut + washer: do NOT fit, put them in a bag with the board (they go on through the enclosure's back panel)."
29,J_USBA,1,,"USB-A receptacle, right angle, THT (Jing Extension 902-131A1011D10100)",USB-A host port (thumb drive / MIDI controller) - USB-A,USB_A_Horizontal_AF90,TH,"LCSC C2345. Through-hole USB-A, flush to the back edge."
30,J_USBC,1,HRO,TYPE-C-31-M-12,USB-C PD power / charge input - USB-C,USB_C_Receptacle_HRO_TYPE-C-31-M-12,TH,"LCSC C165948. USB-C 16-pin receptacle (hybrid SMD/TH), flush to the back edge."
31,"J_USB_BAR,J_USB_UP",2,JST,B4B-PH-K-S,JST PH 4,JST_PH_B4B-PH-K_1x04_P2.00mm_Vertical,TH,"LCSC C131334. JST PH 4-pin, back side (bar screen touch/power, USB hub upstream)."
32,"J_MIDI_IN,J_MIDI_OUT,J_PHONES",3,,PJ-320D-4A,3.5mm TRRS,Jack_3.5mm_PJ320D_Horizontal,TH,LCSC C95562.
33,L_3V3,1,Sunlord,"MWSA0603S-2R2MT (2.2uH, 8 A)",3V3 inductor - 2.2uH,L_Sunlord_MWSA0603S,SMD,LCSC C408445.
34,"L_5V1,L_5V2",2,Sunlord,"MWSA0603S-3R3MT (3.3uH, 8 A)",3.3uH,L_Sunlord_MWSA0603S,SMD,LCSC C408446.
35,L_CHG,1,Sunlord,"MWSA0603S-2R2MT (2.2 uH, 10 A)",Charger inductor - 2.2uH,L_Sunlord_MWSA0603S,SMD,LCSC C408445.
36,"LED_FS1,LED_FS2,LED_FS3,LED_FS4,LED_FS5,LED_FS6,LED_FS7,LED_FS8,LED_FS9,LED_FS10",10,,"5 mm yellow LED (XINGLIGHT XL-504UYC), on a 10 mm LED spacer",LED 5mm,LED_D5.0mm,TH,"LCSC C2895487. 5 mm yellow LED, long leg (+) in the square pad, stands 15 mm proud for the top plate."
37,"OLED_A,OLED_B,OLED_FS1,OLED_FS2,OLED_FS3,OLED_FS4,OLED_FS5,OLED_FS6,OLED_FS7,OLED_FS8,OLED_FS9,OLED_FS10,OLED_K1,OLED_K2,OLED_K3,OLED_K4,OLED_K5,OLED_K6",18,,"0.91 inch 128x32 I2C OLED module, SSD1306, 4-pin (GND VCC SCL SDA)",OLED 0.91in,OLED_091_I2C_Socket,TH,"0.91"" 128x32 I2C OLED module (SSD1306, 4 pins at 2.54 mm: GND VCC SCL SDA). Solder straight into the socket holes, screen facing up. If the module's pin order is VCC GND SCL SDA, move the two 0R links next to it from A to B."
38,Q_FAN,1,Alpha&Omega,AO3400A,Fan switch - AO3400A,SOT-23,SMD,LCSC C20917.
39,Q_REV,1,Alpha&Omega,AO4407A,Reverse-battery protection P-MOSFET - AO4407A,SOIC-8_3.9x4.9mm_P1.27mm,SMD,LCSC C16072.
40,"R1,R2,R3,R4,R5,R6,R18,R31,R33,R36,R38,R40,R42,R50,R56,R73,R79,R85,R91,R97,R103,R109,R115,R121,R127,R229",26,,,100R,R_0603_1608Metric,SMD,LCSC C22775.
41,"R8,R70,R75,R76,R81,R82,R87,R88,R93,R94,R99,R100,R105,R106,R111,R112,R117,R118,R123,R124,R129,R130,R136,R137,R143,R144,R150,R151,R157,R158,R164,R165,R171,R172,R176,R177,R181,R182",38,,,0R,R_0603_1608Metric,SMD,LCSC C21189.
42,"R9,R10",2,,,900k,R_0603_1608Metric,SMD,LCSC C55585693.
43,R11,1,,,11k,R_0603_1608Metric,SMD,LCSC C25950.
44,"R12,R15",2,,,21k,R_0603_1608Metric,SMD,LCSC C22956.
45,R13,1,,,8.2k,R_0603_1608Metric,SMD,LCSC C25981.
46,"R14,R16,R19,R20,R25,R27,R29,R43,R45,R51,R54,R57,R60,R61,R133,R134,R135,R140,R141,R142,R147,R148,R149,R154,R155,R156,R161,R162,R163,R168,R169,R170,R185,R186,R187,R188,R189,R227,R228,R230",40,,,10k,R_0603_1608Metric,SMD,LCSC C25804.
47,"R17,R72",2,,,15k,R_0603_1608Metric,SMD,LCSC C22809.
48,"R21,R23,R34,R44,R46,R47,R48,R71",8,,,100k,R_0603_1608Metric,SMD,LCSC C25803.
49,"R22,R53,R59,R191,R192,R193,R194,R195,R196,R197,R198,R199,R200,R201,R202,R203,R204,R205,R206,R207,R208,R209,R210,R211,R212,R213,R214,R215,R216,R217,R218,R219,R220,R221,R222,R223,R224,R225,R226",39,,,4.7k,R_0603_1608Metric,SMD,LCSC C23162.
50,"R24,R26",2,,,57.6k,R_0603_1608Metric,SMD,LCSC C23082.
51,R28,1,,,33.2k,R_0603_1608Metric,SMD,LCSC C23003.
52,"R30,R32,R35,R37,R39,R41",6,,,470R,R_0603_1608Metric,SMD,LCSC C23179.
53,"R49,R55",2,,,1M,R_0603_1608Metric,SMD,LCSC C22935.
54,"R52,R58",2,,,30k,R_0603_1608Metric,SMD,LCSC C22984.
55,"R62,R64",2,,,270R,R_0603_1608Metric,SMD,LCSC C22966.
56,"R63,R65",2,,,150R,R_0603_1608Metric,SMD,LCSC C22808.
57,R66,1,,,220R,R_0603_1608Metric,SMD,LCSC C22962.
58,R67,1,,,2.2k,R_0603_1608Metric,SMD,LCSC C4190.
59,R68,1,,,10R,R_0603_1608Metric,SMD,LCSC C22859.
60,R69,1,,,33R,R_0603_1608Metric,SMD,LCSC C23140.
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

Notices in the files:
README.md:
License: MIT
